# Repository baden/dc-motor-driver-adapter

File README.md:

# dc-motor-driver-adapter

Тут буде і плата і програма.

## Встановлення інструментів

https://github.com/riscv-software-src/homebrew-riscv

```bash
brew tap riscv-software-src/riscv
brew install riscv-tools
brew install riscv-openocd
brew test riscv-tools
/opt/homebrew/opt/riscv-gnu-toolchain/bin/riscv64-unknown-elf-gcc --version
```

/opt/homebrew/opt/riscv-openocd/bin/openocd

Во, подивиться це:

https://github.com/wagiminator/CH32V003-GameConsole/tree/main

Ще це:
https://github.com/wagiminator/MCU-Templates

Ще тут купа посилань:
https://github.com/wagiminator/Development-Boards/tree/main/CH32V003A4M6_DevBoard

https://github.com/AlessandroAU/ESP32-CRSF-Packet-Gen/blob/master/CRSF_testcode/CRSF.h
https://px4.github.io/Firmware-Doxygen/d9/dd2/crsf_8cpp_source.html

https://github.com/vedderb/bldc_uart_comm_stm32f4_discovery/blob/c19a6283e187040f25aa52e213673938db054d06/bldc_interface.c#L567

https://vedder.se/2015/10/communicating-with-the-vesc-using-uart/

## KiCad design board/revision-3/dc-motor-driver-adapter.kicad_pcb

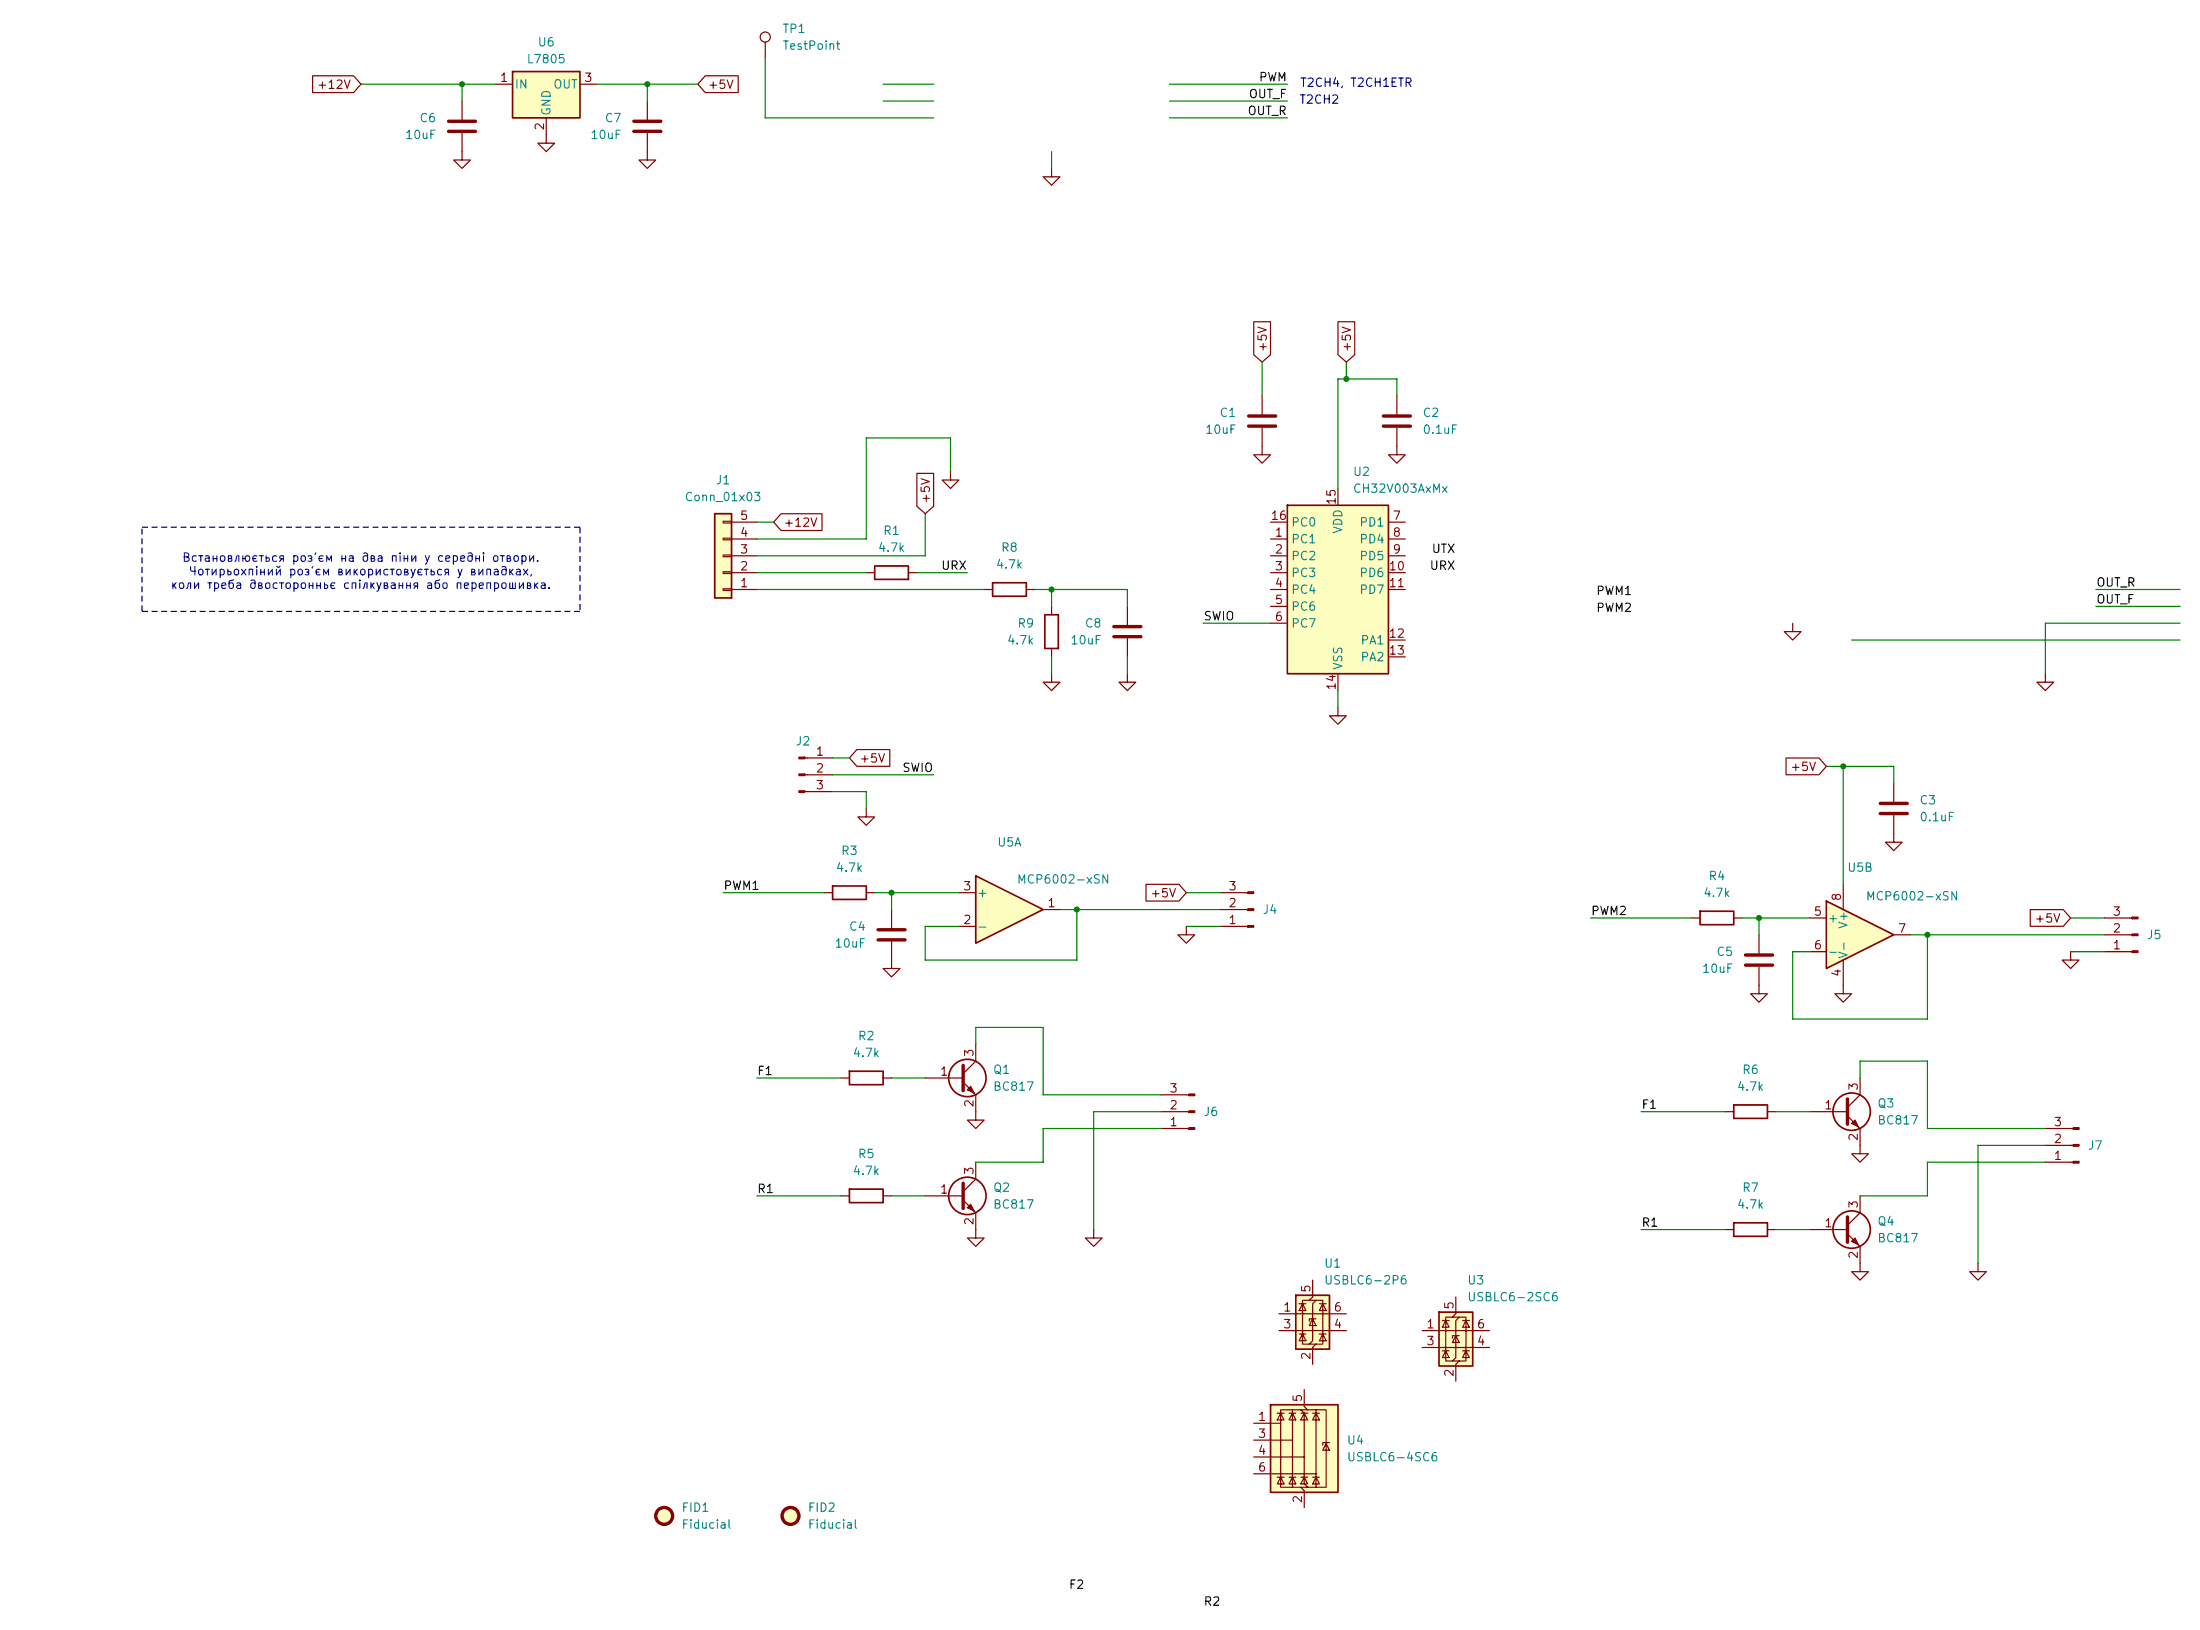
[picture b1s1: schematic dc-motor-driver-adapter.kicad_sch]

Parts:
C1, C4, C5, C6, C7, C8: 10uF; C_0805_2012Metric
C2, C3: 0.1uF; C_0603_1608Metric
FID1, FID2: Fiducial; Fiducial_1mm_Mask2mm
J1: Conn_01x03; JST_PH_S5B-PH-K_1x05_P2.00mm_Horizontal
J2, J4, J5, J6, J7: Conn_01x03_Pin; JST_PH_B3B-PH-K_1x03_P2.00mm_Vertical
Q1, Q2, Q3, Q4: BC817; SOT-23
R1, R2, R3, R4, R5, R6, R7, R8, R9: 4.7k; R_0603_1608Metric
TP1: TestPoint; TestPoint_Pad_2.0x2.0mm
U1: USBLC6-2P6; SOT-666
U2: CH32V003AxMx; SOP-16_3.9x9.9mm_P1.27mm
U3: USBLC6-2SC6; SOT-23-6
U4: USBLC6-4SC6; SOT-23-6
U5: MCP6002-xSN; SO-8_3.9x4.9mm_P1.27mm
U6: L7805; TO-252-2

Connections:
+5V: C1.1, C2.1, C3.1, C7.1, J1.3, J2.1, J4.3, J5.3, U2.15 (VDD), U5.8 (V+), U6.3 (OUT)
+12V: C6.1, J1.5, U6.1 (IN)
/F1: R2.2, R6.2
/PWM1: R3.2
/PWM2: R4.2
/R1: R5.2, R7.2
/SWIO: J2.2, U2.6 (PC7)
/URX: R1.2
GND: C1.2, C2.2, C3.2, C4.2, C5.2, C6.2, C7.2, C8.2, J1.4, J2.3, J4.1, J5.1, J6.2, J7.2, Q1.2 (E), Q2.2 (E), Q3.2 (E), Q4.2 (E), R9.2, U2.14 (VSS), U5.4 (V-), U6.2 (GND)
unnamed: C8.1, R8.1, R9.1
unnamed: J1.2, R1.1
unnamed: J4.2, U5.1, U5.2 (-)
unnamed: J5.2, U5.6 (-), U5.7
unnamed: J6.1, Q2.3 (C)
unnamed: J6.3, Q1.3 (C)
unnamed: J7.1, Q4.3 (C)
unnamed: J7.3, Q3.3 (C)
unnamed: Q1.1 (B), R2.1
unnamed: Q2.1 (B), R5.1
unnamed: Q3.1 (B), R6.1
unnamed: Q4.1 (B), R7.1
unnamed: J1.1, R8.2
unnamed: C4.1, R3.1, U5.3 (+)
unnamed: C5.1, R4.1, U5.5 (+)

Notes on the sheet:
Встановлюється роз'єм на два піни у середні отвори. Чотирьохпіний роз'єм використовується у випадках, коли треба двосторонньє спілкування або перепрошивка.
T2CH2
T2CH4, T2CH1ETR

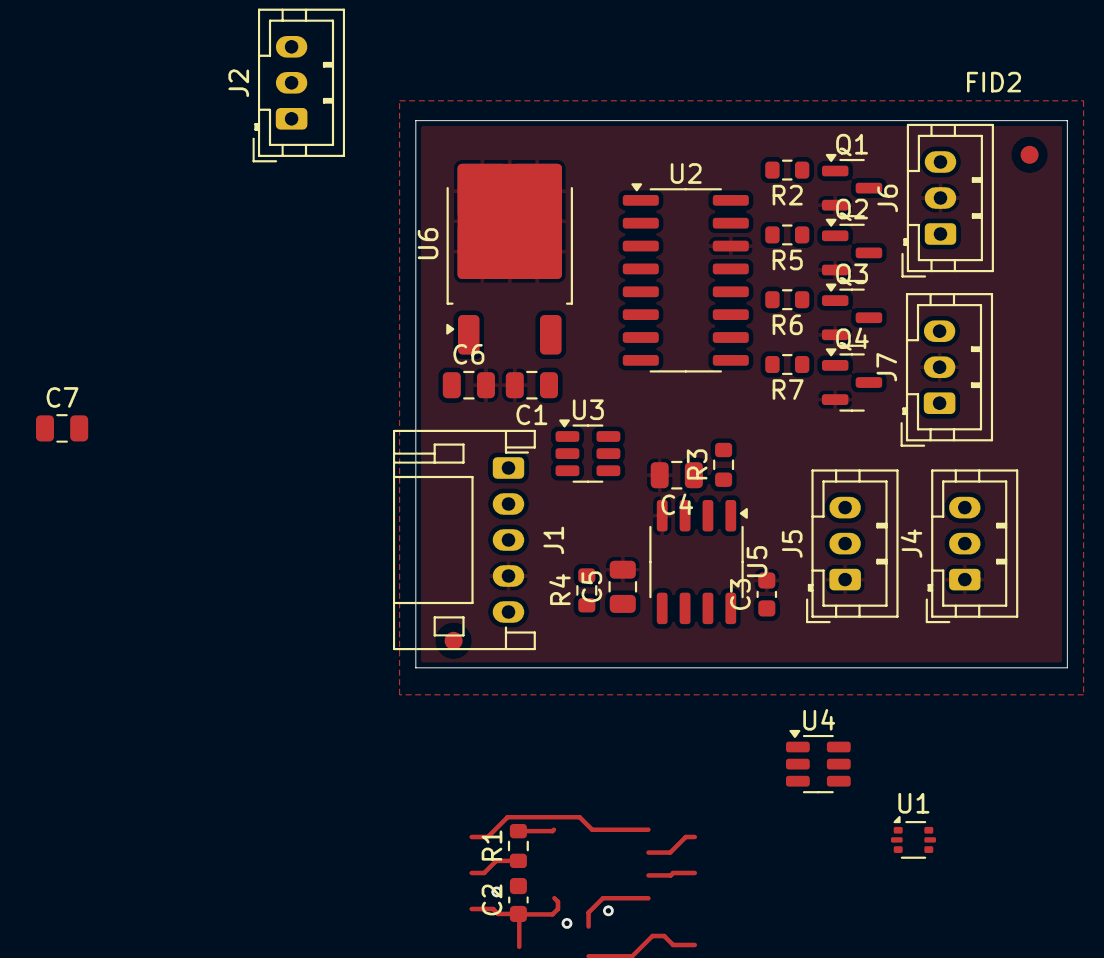
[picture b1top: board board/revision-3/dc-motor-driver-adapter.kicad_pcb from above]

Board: 2 copper layers, 36.2 x 30.4 mm, 33 parts (1 on the bottom side), 19 nets.

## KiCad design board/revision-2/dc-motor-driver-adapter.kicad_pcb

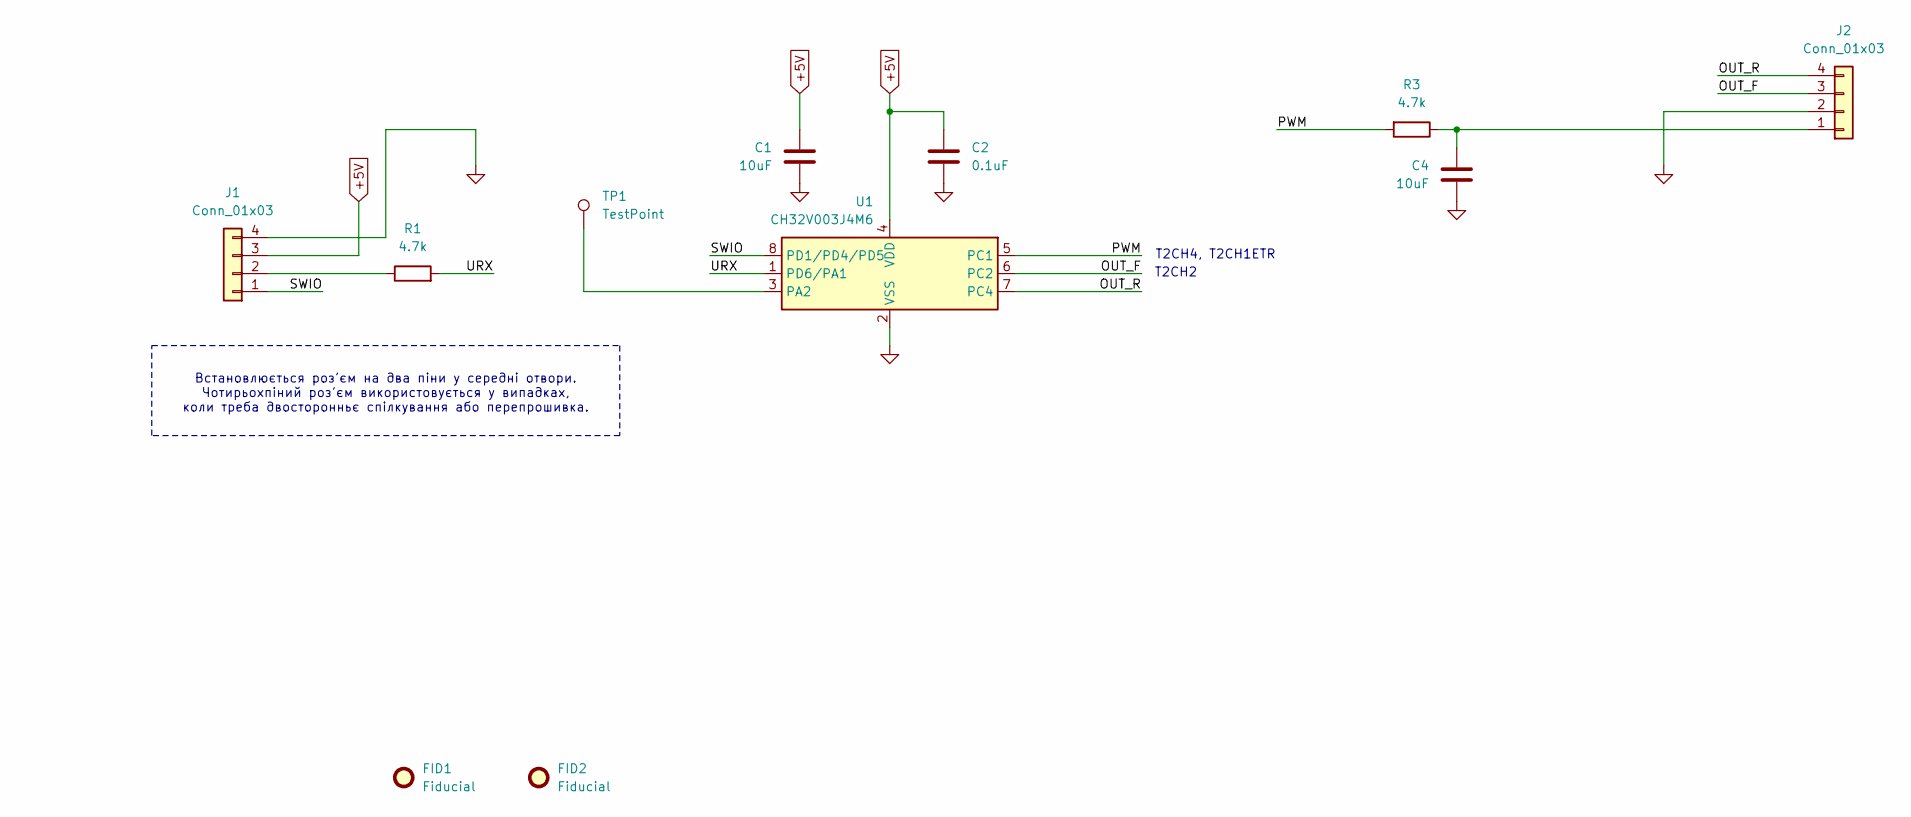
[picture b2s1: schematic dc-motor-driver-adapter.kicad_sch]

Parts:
C1, C4: 10uF; C_0805_2012Metric
C2: 0.1uF; C_0603_1608Metric
FID1, FID2: Fiducial; Fiducial_1mm_Mask2mm
J1, J2: Conn_01x03; JST_PH_S4B-PH-K_1x04_P2.00mm_Horizontal
R1, R3: 4.7k; R_0603_1608Metric
TP1: TestPoint; TestPoint_Pad_2.0x2.0mm
U1: CH32V003J4M6; SOP-8_3.9x4.9mm_P1.27mm

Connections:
+5V: C1.1, C2.1, J1.3, U1.4 (VDD)
/OUT_F: J2.3, U1.6 (PC2)
/OUT_R: J2.4, U1.7 (PC4)
/PWM: R3.2, U1.5 (PC1)
/SWIO: J1.1, U1.8 (PD1/PD4/PD5)
/URX: R1.2, U1.1 (PD6/PA1)
GND: C1.2, C2.2, C4.2, J1.4, J2.2, U1.2 (VSS)
unnamed: J1.2, R1.1
unnamed: C4.1, J2.1, R3.1
unnamed: TP1.1, U1.3 (PA2)

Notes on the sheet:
Встановлюється роз'єм на два піни у середні отвори. Чотирьохпіний роз'єм використовується у випадках, коли треба двосторонньє спілкування або перепрошивка.
T2CH2
T2CH4, T2CH1ETR

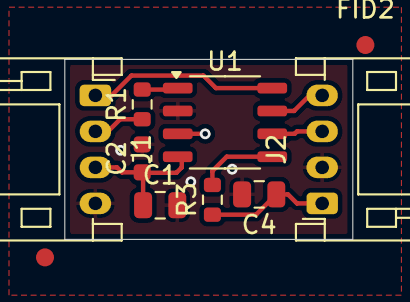
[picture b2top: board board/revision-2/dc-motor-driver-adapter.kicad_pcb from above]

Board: 2 copper layers, 16.0 x 10.0 mm, 11 parts (1 on the bottom side), 10 nets.

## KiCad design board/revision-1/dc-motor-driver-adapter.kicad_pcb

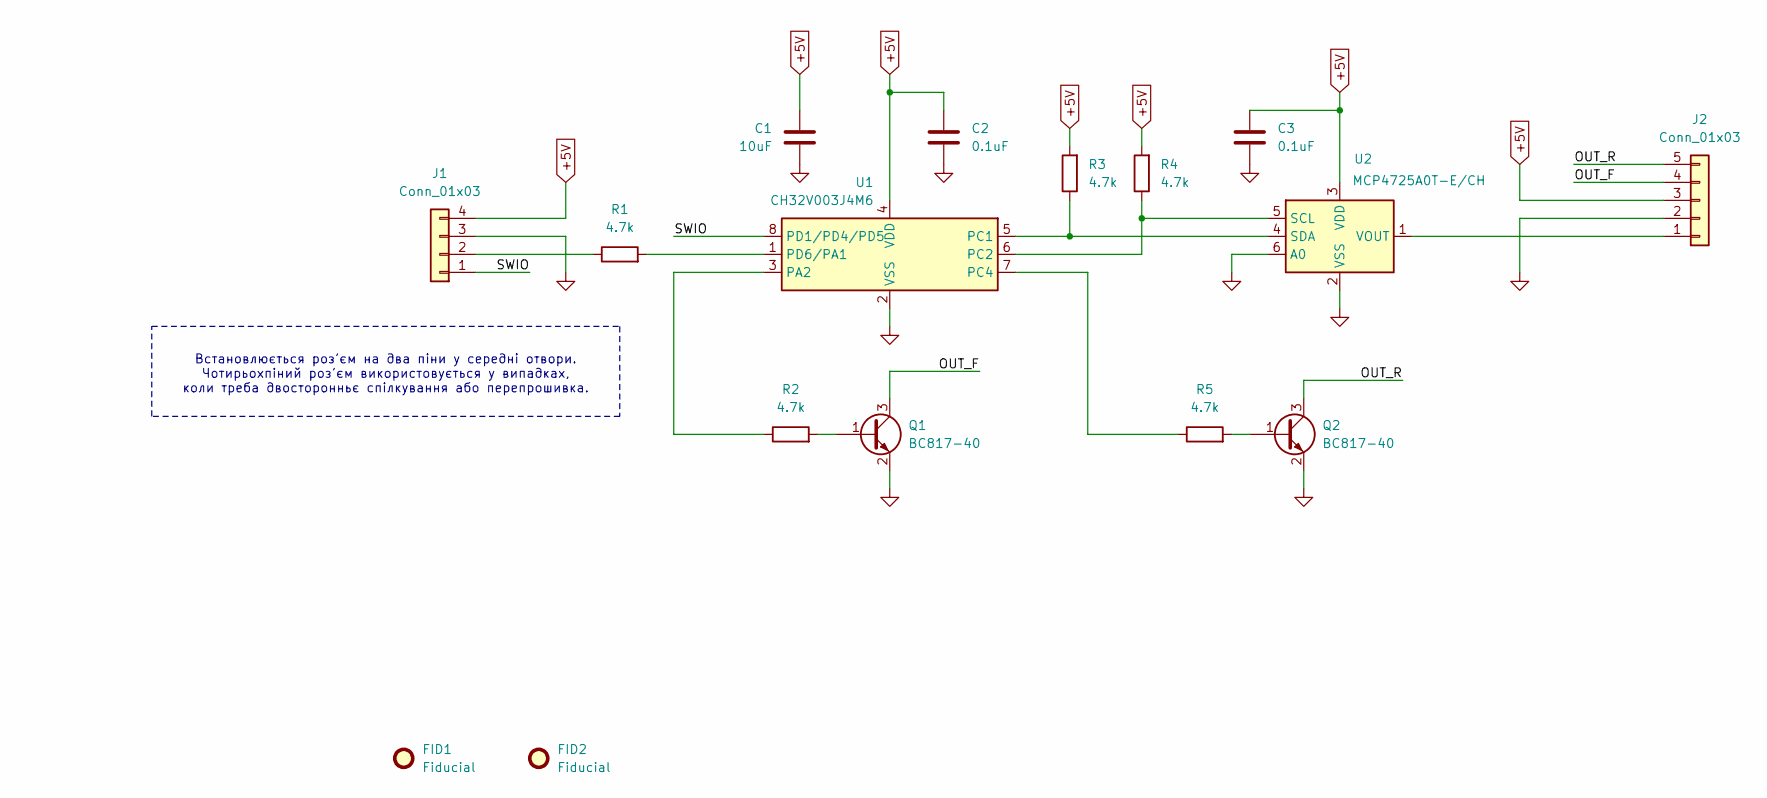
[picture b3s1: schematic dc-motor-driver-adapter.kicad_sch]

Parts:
C1: 10uF; C_0805_2012Metric
C2, C3: 0.1uF; C_0603_1608Metric
FID1, FID2: Fiducial; Fiducial_1mm_Mask2mm
J1: Conn_01x03; JST_XH_S4B-XH-A-1_1x04_P2.50mm_Horizontal
J2: Conn_01x03; JST_XH_S5B-XH-A-1_1x05_P2.50mm_Horizontal
Q1, Q2: BC817-40; SOT-23
R1, R2, R3, R4, R5: 4.7k; R_0603_1608Metric
U1: CH32V003J4M6; SOP-8_3.9x4.9mm_P1.27mm
U2: MCP4725A0T-E/CH; SOT-23-6

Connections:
+5V: C1.1, C2.1, C3.1, J1.4, J2.3, R3.2, R4.2, U1.4 (VDD), U2.3 (VDD)
/OUT_F: J2.4, Q1.3 (C)
/OUT_R: J2.5, Q2.3 (C)
/SWIO: J1.1, U1.8 (PD1/PD4/PD5)
GND: C1.2, C2.2, C3.2, J1.3, J2.2, Q1.2 (E), Q2.2 (E), U1.2 (VSS), U2.2 (VSS), U2.6 (A0)
unnamed: J1.2, R1.1
unnamed: J2.1, U2.1 (VOUT)
unnamed: Q1.1 (B), R2.2
unnamed: Q2.1 (B), R5.2
unnamed: R2.1, U1.3 (PA2)
unnamed: R3.1, U1.5 (PC1), U2.4 (SDA)
unnamed: R4.1, U1.6 (PC2), U2.5 (SCL)
unnamed: R5.1, U1.7 (PC4)
unnamed: R1.2, U1.1 (PD6/PA1)

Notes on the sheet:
Встановлюється роз'єм на два піни у середні отвори. Чотирьохпіний роз'єм використовується у випадках, коли треба двосторонньє спілкування або перепрошивка.

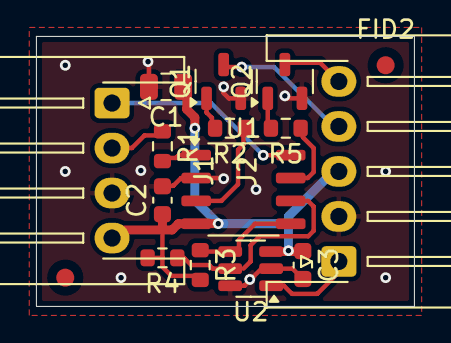
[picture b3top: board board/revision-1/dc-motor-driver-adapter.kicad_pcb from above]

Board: 2 copper layers, 21.0 x 15.0 mm, 16 parts (0 on the bottom side), 14 nets.

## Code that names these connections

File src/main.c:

#include <stdbool.h>
#include "gpio.h"
#include "debug_serial.h"
#include "uart_rx.h"
#include "crsf.h"
#include "dac.h"
#include "system.h"


// Device modes:
// 1 - Керування лебідкою по каналу 12
// 2 - Керування лівим бортом по каналах 1 та 2  (1+2)
// 3 - Керування правим бортом по каналах 1 та 2 (2-1)

#if !defined(DEVICE_MODE)
    #error "DEVICE_MODE is not defined"
#endif
// #define DEVICE_MODE 3

// Керування тільки аналоговим виходом з нулем у середині діапазону
#define DEVICE_ANALOG_ONLY 1

//#define STARTKIT 1

#if defined(STARTKIT)

    #define PIN_LED    PD0   // pin connected to LED (Startkit)

#else

#endif


static inline void init(void)
{
    #if defined(STARTKIT)
        PIN_output(PIN_LED);
        PIN_high(PIN_LED);

        PIN_output(PC0);   // "+" for LED
        PIN_high(PC0);
    #endif

    #if 0
    PIN_input_PD(PD6); // Вхід для PPM (UART) (підтягнутий до землі)
    #endif

    // SYS_init();
    UART_init();
    dac_init();

    #if DEVICE_MODE == 1
        dac_write(2730);        // TODO: Підібрати напругу 12В
    #else
        #if defined(DEVICE_ANALOG_ONLY) && (DEVICE_ANALOG_ONLY == 1)
            dac_write(2047);    // За замовчуванням напруга 1/2
        #else
            dac_write(4095);
        #endif
    #endif

#if 0
    // Configure PD6 as interrupt input
    // The "port" is:
    // 0 for Port A
    // 1 for Port B
    // 2 for Port C
    // 3 for Port D
    #define _portno 3
    #define _pin 6

    RCC->APB2PCENR |= RCC_AFIOEN;
	// Configure the IO as an interrupt.
    AFIO->EXTICR = _portno << (_pin * 2);
	EXTI->INTENR = EXTI_INTENR_MR6; // Enable EXT6
	EXTI->RTENR = EXTI_RTENR_TR6;  // Rising edge trigger
    EXTI->FTENR = EXTI_FTENR_TR6;  // Falling edge trigger

    // enable pin-change-interrupt.
    NVIC_EnableIRQ( EXTI7_0_IRQn );
#endif

#if 0
    RCC->APB2PCENR |= RCC_TIM1EN; // enable TIM1 clock
    // RCC->APB2PRSTR = RCC_TIM1RST;
	// RCC->APB2PRSTR = 0;

	TIM1->ATRLR = 0xffff;
	TIM1->PSC = 47; // 48MHz/(47+1) -> 1µs resolution

    // D2 Capture Input(T1CH1)
    // PA1 - T1CH2

	TIM1->CHCTLR1 = TIM_CC1S_0 | TIM_CC2S_1;

	TIM1->CCER = TIM_CC1E|TIM_CC2E|TIM_CC2P;

	TIM1->CTLR1 = TIM_CEN;

	NVIC_EnableIRQ(TIM1_CC_IRQn);
	TIM1->DMAINTENR = TIM_CC1IE|TIM_CC2IE;    
#endif

//   ADC_init();
//   ADC_input(PIN_PAD);

    // DEBUG_init();
}

#if 0
volatile unsigned int counter = 0;
volatile uint32_t last_value = 0;

void EXTI7_0_IRQHandler( void ) __attribute__((interrupt));
void EXTI7_0_IRQHandler( void ) 
{
    static uint32_t starttime;

    PIN_high(PC1);
    unsigned pin = PIN_read(PD6);

    if(pin != 0) {
        starttime = STK->CNT;
    } else {
        last_value = STK->CNT - starttime;
    }
	EXTI->INTFR = EXTI_INTF_INTF6;
    PIN_low(PC1);
}
#endif

#if DEVICE_MODE == 1

static void rxTo(int val)
{
    if(val < 500) {
        #if defined(STARTKIT)
            PIN_low(PIN_LED);
        #endif
        PIN_high(PC4);
        PIN_low(PA2);
    } else if(val > 1500) {
        #if defined(STARTKIT)
            PIN_low(PIN_LED);
        #endif
        PIN_low(PC4);
        PIN_high(PA2);
    } else {
        #if defined(STARTKIT)
            PIN_high(PIN_LED);
        #endif
        PIN_low(PC4);
        PIN_low(PA2);
    }
}

static void rxFoo()
{
    int val = channel[12 -1];

    // Middle = 1044
    // Low = 191
    // High = 1792
    rxTo(val);
}

#elif (DEVICE_MODE == 2) || (DEVICE_MODE == 3) 

#define LOW_PASS_FILTER
// CRSF center value is 992
#define CENTER_X 992
#define CENTER_Y 992
#define MAX_X 820
#define MAX_Y 820
#define DEAD_ZONE 10

static void rxTo(int dac_val)
{
    #ifdef LOW_PASS_FILTER
        static int last_dac_val = 0;
        int _dac = dac_val;
        dac_val = (dac_val + last_dac_val) / 2;
        last_dac_val = _dac;
    #endif

    if((dac_val < DEAD_ZONE) && (dac_val > -DEAD_ZONE)) {
        #if defined(DEVICE_ANALOG_ONLY) && (DEVICE_ANALOG_ONLY == 1)
            dac_write(2047);
        #else
            dac_write(4095);
            PIN_low(PC4);
            PIN_low(PA2);
        #endif
    } else {
        #if defined(DEVICE_ANALOG_ONLY) && (DEVICE_ANALOG_ONLY == 1)
            dac_val *= 5; // (channel[3 -1] - 1000) * 4096 / 1000;
            dac_val += 2048;
            if(dac_val < 0) {
                dac_val = 0;
            } else if(dac_val > 4095) {
                dac_val = 4095;
            }
            dac_write(dac_val);
        #else
            if(dac_val > 0) {
                PIN_low(PC4);
                PIN_high(PA2);
            } else {
                PIN_low(PA2);
                PIN_high(PC4);
                dac_val = -dac_val;
            }

            dac_val *= 5; // (channel[3 -1] - 1000) * 4096 / 1000;
            if(dac_val < 0) {
                dac_val = 0;
            } else if(dac_val > 4095) {
                dac_val = 4095;
            }
            dac_write(4095-dac_val);

        #endif

    }
}

static void rxFoo()
{
    // bool in_dead_zone = false;

    int X = channel[1 -1] - CENTER_X;   // -MAX_X to MAX_X
    int Y = channel[2 -1] - CENTER_Y;   // -MAX_Y to MAX_Y

    #if (DEVICE_MODE == 2)
        int dac_val = (X+Y);
    #else
        int dac_val = (Y-X);
    #endif
    rxTo(dac_val);
}

#endif

int main(void)
{
    // PIN_output(PC1);

    PIN_output(PC4);    // Right
    PIN_low(PC4);
    PIN_output(PA2);    // Left
    PIN_low(PA2);

    init();

    #if defined(STARTKIT)
        PIN_low(PIN_LED);
    #endif

    // DEBUG_println("Start");

    #define RX_TIMEOUT  500 * DLY_MS_TIME

    uint32_t next_tick = STK->CNT + RX_TIMEOUT;

//   while(((int32_t)(STK->CNT - end)) < 0);


    while(1)
    {
        // #if defined(STARTKIT)
        //     PIN_toggle(PIN_LED);
        // #endif
        // DLY_ms(500);

        if(UART_available()) {
            char c = USART1->DATAR;
            rxParseByte(c);
            // PIN_toggle(PIN_LED);

            if(crsf_frame_ready) {
                crsf_frame_ready = false;
                rxFoo();
                next_tick = STK->CNT + RX_TIMEOUT;
            }
        }

        if(((int32_t)(STK->CNT - next_tick)) > 0) {
            next_tick = STK->CNT + RX_TIMEOUT;

            #if DEVICE_MODE == 1
                rxTo(1000);
            #else
                rxTo(0);
            #endif
            // next_tick += 1000 * DLY_MS_TIME;
        // //     // dac_write(0);

        //     PIN_toggle(PC4);
        // //     // PIN_high(PC4);

        }

    #if 0
        counter++;
        uint32_t duration = last_value / (F_CPU / 1000000);        // Значення у мікросекундах

        DEBUG_printf("Counter: %d  Last value: %d  Duration: %d\n", counter, last_value, duration);
    #endif
    }
}

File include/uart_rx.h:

// ===================================================================================
// Basic UART Functions (RX only) for CH32V003                                * v1.1 *
// ===================================================================================
//
// Functions available:
// --------------------
// UART_init()              Init UART with default BAUD rate (115200)
// UART_available()         Check if there is something to read
// UART_read()              Read character via UART
//
// UART_setBaud(n)          Set BAUD rate
// UART_setStopBits(n)      Set number of stop bits (n = 1, 2)
// UART_setNoParity()       Set no parity bit
// UART_setOddParity()      Set parity bit, odd
// UART_setEvenParity()     Set parity bit, even
//
// UART_enable()            Enable USART
// UART_disable()           Disable USART
//
// USART1 pin mapping (set below in UART parameters):
// --------------------------------------------------
// UART_MAP   0     1     2     3
// RX-pin    PD6   PD1   PD5   PC1
//
// 2023 by Stefan Wagner:   https://github.com/wagiminator

#pragma once

#ifdef __cplusplus
extern "C" {
#endif

#include "system.h"

// UART Parameters
// #define UART_BAUD             115200      // default UART baud rate
#define UART_BAUD             19200         // default UART baud rate for CRSF protocol is 420000
#define UART_MAP              0           // UART pin remapping (see above)

// UART Macros
#define UART_available()      (USART1->STATR & USART_STATR_RXNE)  // ready to read
#define UART_setBAUD(n)       USART1->BRR = ((2*F_CPU/(n))+1)/2;  // set BAUD rate
#define UART_setStopBits(n)   (n==2 ? (USART1->CTLR2 |= ((uint32_t)1<<13) : (USART1->CTLR2 &= ~((uint32_t)1<<13)))
#define UART_setEvenParity()  {USART1->CTLR1 |= USART_CTLR1_PCE; USART1->CTLR1 &= ~USART_CTLR1_PS;}
#define UART_setOddParity()   {USART1->CTLR1 |= USART_CTLR1_PCE; USART1->CTLR1 |=  USART_CTLR1_PS;}
#define UART_setNoParity()    USART1->CTLR1 &= ~USART_CTLR1_PCE
#define UART_enable()         USART1->CTLR1 |= USART_CTLR1_UE     // enable USART
#define UART_disable()        USART1->CTLR1 &= ~USART_CTLR1_UE    // disable USART

// UART Functions
void UART_init(void);                     // init UART with default BAUD rate
char UART_read(void);                     // read character via UART

#ifdef __cplusplus
};
#endif

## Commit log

2024-04-09 Initial commit.
2024-04-10 Плата замовлена.
2024-04-30 Програму будемо писати прям тут.
2024-05-11 О. Шось скомпілював і навіть прошив, і все, бляха, працює.
2024-05-11 О, додав UART на 115200. Поки використовую для відлагодження.
2024-05-11 UART замінен на Debug. TX only.
2024-05-11 Шось воно незрозуміло якось працює. Нахрін с пляжа.
2024-05-11 Хрін знає як працює капче. Спробую переробити на просто таймер та переривання.
2024-05-11 Почистив від зайвого коду.
2024-05-27 Тестова реалізація CRSF.
2024-05-27 Ревізія два - мега-спрощена.
2024-06-16 Починаю працювати над I2C DAC.
2024-06-17 Начебто повинно працювати. Поїду подивклюсь як воно себе веде на тачці.
2024-06-24 Збереження.
2024-06-25 Додан таймаут для приймача.
2024-07-10 Додана підтримка VESC-контроллерів через ADC вхід.
2024-08-13 Сгенеровані хекси для лівого та правого борта. Та хекс для лебідки.
